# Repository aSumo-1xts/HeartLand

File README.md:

# HeartLand

Ableton LiveでDJをするためのUSB-MIDIコントローラ。

Learn more: https://blog.1xtelescope.com/posts/HeartLand.html

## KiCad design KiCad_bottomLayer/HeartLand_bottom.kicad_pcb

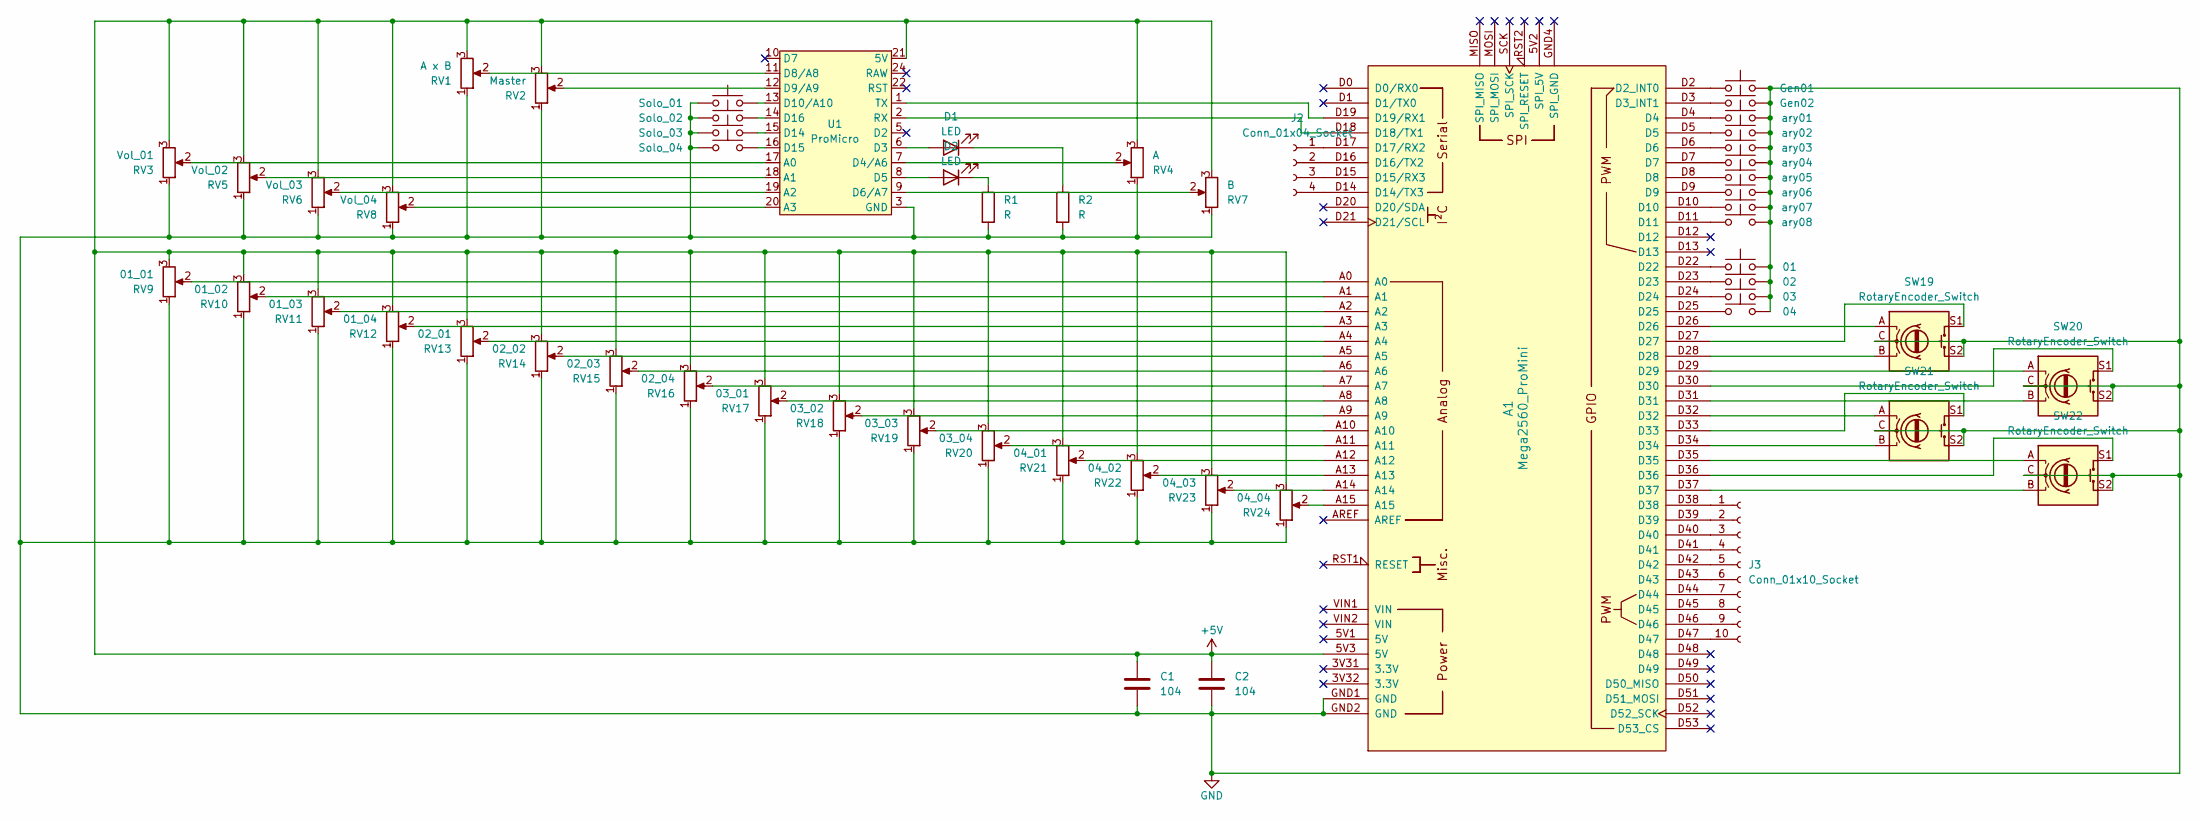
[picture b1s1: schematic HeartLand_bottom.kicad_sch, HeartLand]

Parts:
A1: Mega2560_ProMini; Clone_Mega2560_Pro_Socket
C1, C2: 104; C_Disc_D3.0mm_W1.6mm_P2.50mm
D1, D2: LED; LED_D10.0mm
J2: Conn_01x04_Socket; PinSocket_2x02_P2.00mm_Horizontal
J3: Conn_01x10_Socket; PinSocket_2x05_P2.54mm_Horizontal
R1, R2: R; R_Axial_DIN0204_L3.6mm_D1.6mm_P5.08mm_Horizontal
RV1: A x B; Potentiometer_Bourns_PTA4543_Single_Slide
RV2: Master; Potentiometer_Bourns_PTA4543_Single_Slide
RV3: Vol_01; Potentiometer_Bourns_PTA4543_Single_Slide
RV4: A; Potentiometer_Alps_RK09K_Single_Vertical
RV5: Vol_02; Potentiometer_Bourns_PTA4543_Single_Slide
RV6: Vol_03; Potentiometer_Bourns_PTA4543_Single_Slide
RV7: B; Potentiometer_Alps_RK09K_Single_Vertical
RV8: Vol_04; Potentiometer_Bourns_PTA4543_Single_Slide
RV9: 01_01; Potentiometer_Alps_RK09K_Single_Vertical
RV10: 01_02; Potentiometer_Alps_RK09K_Single_Vertical
RV11: 01_03; Potentiometer_Alps_RK09K_Single_Vertical
RV12: 01_04; Potentiometer_Alps_RK09K_Single_Vertical
RV13: 02_01; Potentiometer_Alps_RK09K_Single_Vertical
RV14: 02_02; Potentiometer_Alps_RK09K_Single_Vertical
RV15: 02_03; Potentiometer_Alps_RK09K_Single_Vertical
RV16: 02_04; Potentiometer_Alps_RK09K_Single_Vertical
RV17: 03_01; Potentiometer_Alps_RK09K_Single_Vertical
RV18: 03_02; Potentiometer_Alps_RK09K_Single_Vertical
RV19: 03_03; Potentiometer_Alps_RK09K_Single_Vertical
RV20: 03_04; Potentiometer_Alps_RK09K_Single_Vertical
RV21: 04_01; Potentiometer_Alps_RK09K_Single_Vertical
RV22: 04_02; Potentiometer_Alps_RK09K_Single_Vertical
RV23: 04_03; Potentiometer_Alps_RK09K_Single_Vertical
RV24: 04_04; Potentiometer_Alps_RK09K_Single_Vertical
SW1: Gen01; SW_Cherry_MX_1.00u_PCB
SW2: Solo_01; SW_Cherry_MX_1.00u_PCB
SW3: Gen02; SW_Cherry_MX_1.00u_PCB
SW4: Solo_02; SW_Cherry_MX_1.00u_PCB
SW5: ary01; SW_Cherry_MX_1.00u_PCB
SW6: Solo_03; SW_Cherry_MX_1.00u_PCB
SW7: ary02; SW_Cherry_MX_1.00u_PCB
SW8: Solo_04; SW_Cherry_MX_1.00u_PCB
SW9: ary03; SW_Cherry_MX_1.00u_PCB
SW10: ary04; SW_Cherry_MX_1.00u_PCB
SW11: ary05; SW_Cherry_MX_1.00u_PCB
SW12: ary06; SW_Cherry_MX_1.00u_PCB
SW13: ary07; SW_Cherry_MX_1.00u_PCB
SW14: ary08; SW_Cherry_MX_1.00u_PCB
SW15: 01; SW_Cherry_MX_1.00u_PCB
SW16: 02; SW_Cherry_MX_1.00u_PCB
SW17: 03; SW_Cherry_MX_1.00u_PCB
SW18: 04; SW_Cherry_MX_1.00u_PCB
SW19, SW20, SW21, SW22: RotaryEncoder_Switch; RotaryEncoder_Alps_EC12E-Switch_Vertical_H20mm
U1: ProMicro; Sparkfun_Pro_Micro

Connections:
+5V: A1.5V3 (5V), C1.1, C2.1, RV1.3, RV2.3, RV3.3, RV4.3, RV5.3, RV6.3, RV7.3, RV8.3, RV9.3, RV10.3, RV11.3, RV12.3, RV13.3, RV14.3, RV15.3, RV16.3, RV17.3, RV18.3, RV19.3, RV20.3, RV21.3, RV22.3, RV23.3, RV24.3, U1.21 (5V)
GND: A1.GND1 (GND), A1.GND2 (GND), C1.2, C2.2, R1.2, R2.2, RV1.1, RV1.MP, RV2.1, RV2.MP, RV3.1, RV3.MP, RV4.1, RV4.MP, RV5.1, RV5.MP, RV6.1, RV6.MP, RV7.1, RV7.MP, RV8.1, RV8.MP, RV9.1, RV9.MP, RV10.1, RV10.MP, RV11.1, RV11.MP, RV12.1, RV12.MP, RV13.1, RV13.MP, RV14.1, RV14.MP, RV15.1, RV15.MP, RV16.1, RV16.MP, RV17.1, RV17.MP, RV18.1, RV18.MP, RV19.1, RV19.MP, RV20.1, RV20.MP, RV21.1, RV21.MP, RV22.1, RV22.MP, RV23.1, RV23.MP, RV24.1, RV24.MP, SW1.2, SW2.1, SW3.2, SW4.1, SW5.1, SW6.1, SW7.1, SW8.1, SW9.1, SW10.1, SW11.1, SW12.1, SW13.1, SW14.1, SW15.1, SW16.1, SW17.1, SW18.1, SW19.C, SW19.MP, SW19.S2, SW20.C, SW20.MP, SW20.S2, SW21.C, SW21.MP, SW21.S2, SW22.C, SW22.MP, SW22.S2, U1.3 (GND), U1.4 (GND), U1.23 (GND)
unnamed: A1.D2 (D2_INT0), SW1.1
unnamed: A1.D3 (D3_INT1), SW3.1
unnamed: A1.D14 (D14/TX3), J2.4
unnamed: A1.D15 (D15/RX3), J2.3
unnamed: A1.D16 (D16/TX2), J2.2
unnamed: A1.D17 (D17/RX2), J2.1
unnamed: A1.D18 (D18/TX1), U1.2 (RX)
unnamed: A1.D19 (D19/RX1), U1.1 (TX)
unnamed: A1.A0, RV9.2
unnamed: A1.A1, RV10.2
unnamed: A1.A2, RV11.2
unnamed: A1.A3, RV12.2
unnamed: A1.A4, RV13.2
unnamed: A1.A5, RV14.2
unnamed: A1.A6, RV15.2
unnamed: A1.A7, RV16.2
unnamed: A1.A8, RV17.2
unnamed: A1.A9, RV18.2
unnamed: A1.A10, RV19.2
unnamed: A1.A11, RV20.2
unnamed: A1.A12, RV21.2
unnamed: A1.A13, RV22.2
unnamed: A1.A14, RV23.2
unnamed: A1.A15, RV24.2
unnamed: A1.D4, SW5.2
unnamed: A1.D5, SW7.2
unnamed: A1.D6, SW9.2
unnamed: A1.D7, SW10.2
unnamed: A1.D8, SW11.2
unnamed: A1.D9, SW12.2
unnamed: A1.D10, SW13.2
unnamed: A1.D11, SW14.2
unnamed: A1.D22, SW15.2
unnamed: A1.D23, SW16.2
unnamed: A1.D24, SW17.2
unnamed: A1.D25, SW18.2
unnamed: A1.D26, SW19.A
unnamed: A1.D27, SW19.S1
unnamed: A1.D28, SW19.B
unnamed: A1.D29, SW20.A
unnamed: A1.D30, SW20.S1
unnamed: A1.D31, SW20.B
unnamed: A1.D32, SW21.A
unnamed: A1.D33, SW21.S1
unnamed: A1.D34, SW21.B
unnamed: A1.D35, SW22.A
unnamed: A1.D36, SW22.S1
unnamed: A1.D37, SW22.B
unnamed: D1.2 (A), U1.6 (D3)
unnamed: D1.1 (K), R2.1
unnamed: D2.2 (A), U1.8 (D5)
unnamed: D2.1 (K), R1.1
unnamed: A1.D38, J3.1
unnamed: A1.D39, J3.2
unnamed: A1.D40, J3.3
unnamed: A1.D41, J3.4
unnamed: A1.D42, J3.5
unnamed: A1.D43, J3.6
unnamed: A1.D44, J3.7
unnamed: A1.D45, J3.8
unnamed: A1.D46, J3.9
unnamed: A1.D47, J3.10
unnamed: RV3.2, U1.17 (A0)
unnamed: RV5.2, U1.18 (A1)
unnamed: RV6.2, U1.19 (A2)
unnamed: RV8.2, U1.20 (A3)
unnamed: RV4.2, U1.7 (D4/A6)
unnamed: RV7.2, U1.9 (D6/A7)
unnamed: RV1.2, U1.11 (D8/A8)
unnamed: RV2.2, U1.12 (D9/A9)
unnamed: SW2.2, U1.13 (D10/A10)
unnamed: SW6.2, U1.15 (D14)
unnamed: SW8.2, U1.16 (D15)
unnamed: SW4.2, U1.14 (D16)

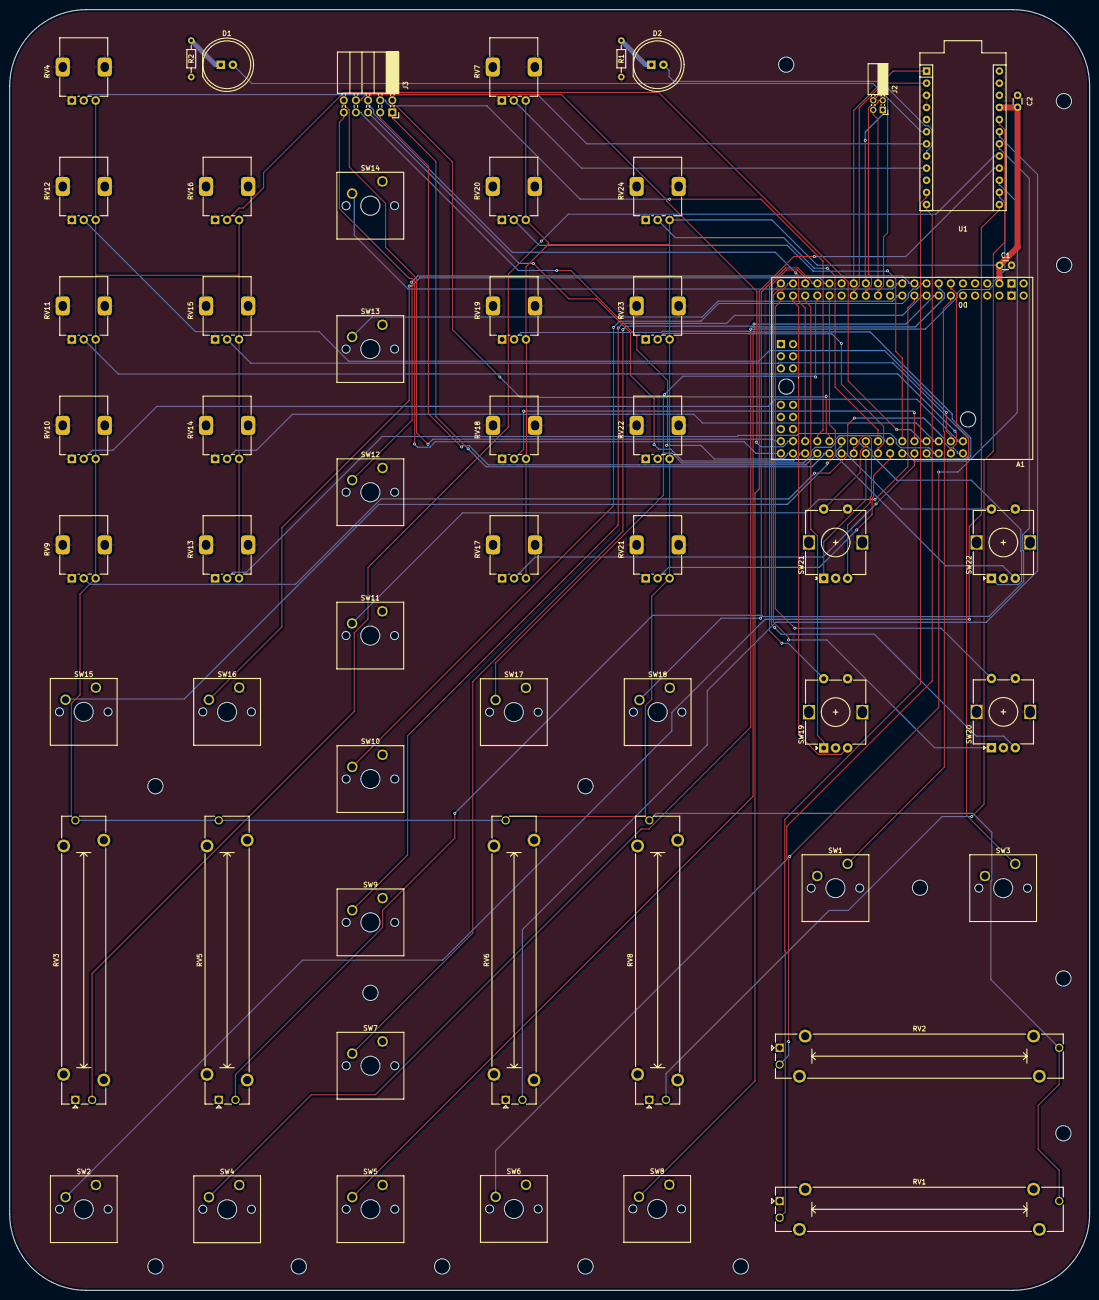
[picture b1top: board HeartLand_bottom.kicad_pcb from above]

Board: 2 copper layers, 226.0 x 268.0 mm, 70 parts (0 on the bottom side), 76 nets.

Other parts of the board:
M3, M3#2, M3#3, M3#4, M3#5, M3#6, M3#7, M3#8, M3#9, M3#10, M3#11, M3#12, M3#13, M3#14: MountingHole_3.2mm_M3

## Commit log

2025-04-22 update: README.mdを編集
2025-04-29 add: KiCadファイル3種を追加
2025-04-29 add: Arduinoスケッチを追加
2025-05-09 update: READMEのバッジを編集
2025-05-09 add: arduino-cliを導入
2025-05-09 update: Actionの発動条件を変更

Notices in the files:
README.md:
License: GPL v3
